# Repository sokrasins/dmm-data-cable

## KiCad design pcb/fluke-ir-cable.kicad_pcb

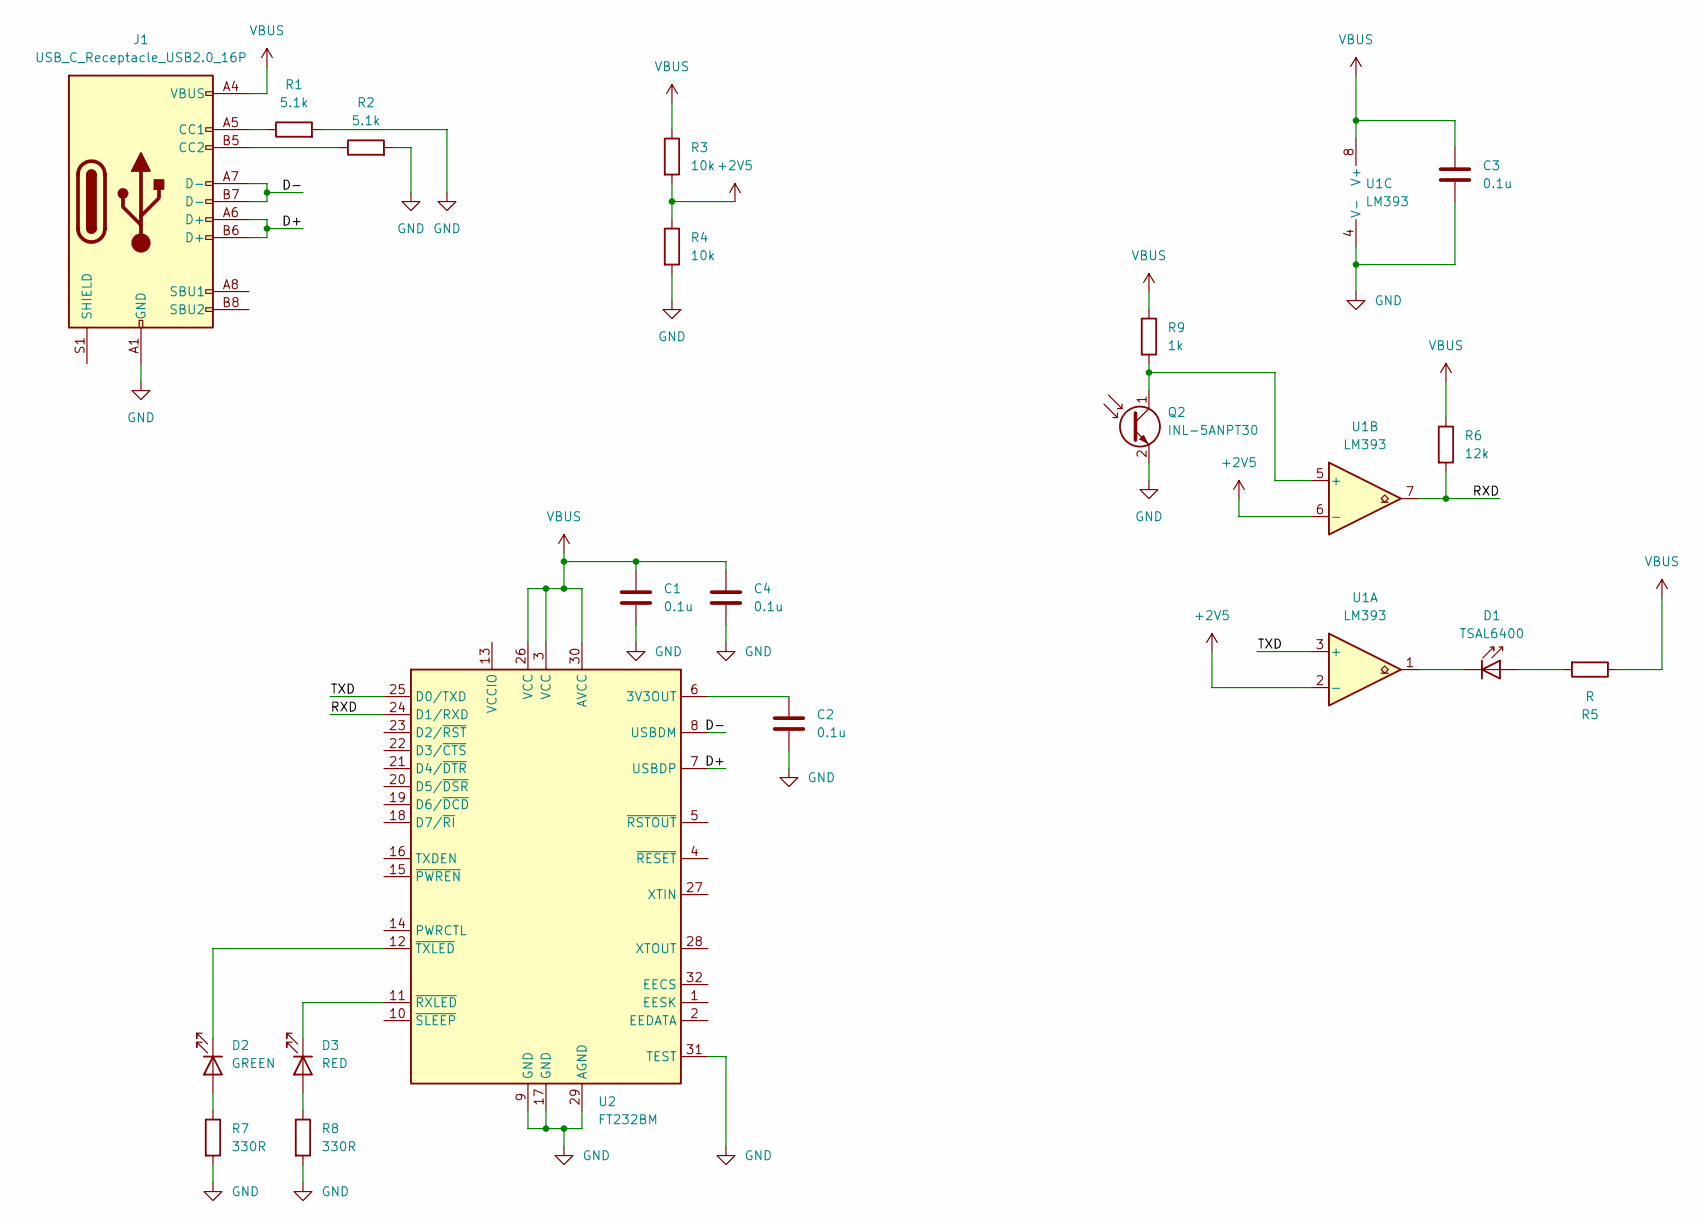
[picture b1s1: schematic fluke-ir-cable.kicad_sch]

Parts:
C1, C2, C3, C4: 0.1u; C_0603_1608Metric_Pad1.08x0.95mm_HandSolder
D1: TSAL6400; LED_D5.0mm_Clear
D2: GREEN; LED_0201_0603Metric_Pad0.64x0.40mm_HandSolder
D3: RED; LED_0201_0603Metric_Pad0.64x0.40mm_HandSolder
J1: USB_C_Receptacle_USB2.0_16P; USB_C_Receptacle_GCT_USB4105-xx-A_16P_TopMnt_Horizontal
Q2: INL-5ANPT30; LED_D5.0mm_Clear
R1, R2: 5.1k; R_0603_1608Metric_Pad0.98x0.95mm_HandSolder
R3, R4: 10k; R_0603_1608Metric_Pad0.98x0.95mm_HandSolder
R5: R; R_0603_1608Metric_Pad0.98x0.95mm_HandSolder
R6: 12k; R_0603_1608Metric_Pad0.98x0.95mm_HandSolder
R7, R8: 330R; R_0603_1608Metric_Pad0.98x0.95mm_HandSolder
R9: 1k; R_0603_1608Metric_Pad0.98x0.95mm_HandSolder
U1: LM393; TSSOP-8_4.4x3mm_P0.65mm
U2: FT232BM; LQFP-32_7x7mm_P0.8mm

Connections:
+2V5: R3.2, R4.1, U1.2 (-), U1.6 (-)
/D+: J1.A6 (D+), J1.B6 (D+), U2.7 (USBDP)
/D-: J1.A7 (D-), J1.B7 (D-), U2.8 (USBDM)
/RXD: R6.2, U1.7, U2.24 (D1/RXD)
/TXD: U1.3 (+), U2.25 (D0/TXD)
GND: C1.2, C2.2, C3.2, C4.2, J1.A1 (GND), J1.A12 (GND), J1.B1 (GND), J1.B12 (GND), Q2.2 (E), R1.2, R2.2, R4.2, R7.2, R8.2, U1.4 (V-), U2.9 (GND), U2.17 (GND), U2.29 (AGND), U2.31 (TEST)
unnamed: D1.2 (A), R5.2
unnamed: D1.1 (K), U1.1
unnamed: D2.2 (A), R7.1
unnamed: D2.1 (K), U2.12 (~TXLED)
unnamed: D3.2 (A), R8.1
unnamed: D3.1 (K), U2.11 (~RXLED)
unnamed: J1.A5 (CC1), R1.1
unnamed: J1.B5 (CC2), R2.1
unnamed: Q2.1 (C), R9.2, U1.5 (+)
unnamed: C2.1, U2.6 (3V3OUT)
VBUS: C1.1, C3.1, C4.1, J1.A4 (VBUS), J1.A9 (VBUS), J1.B4 (VBUS), J1.B9 (VBUS), R3.1, R5.1, R6.1, R9.1, U1.8 (V+), U2.3 (VCC), U2.26 (VCC), U2.30 (AVCC)

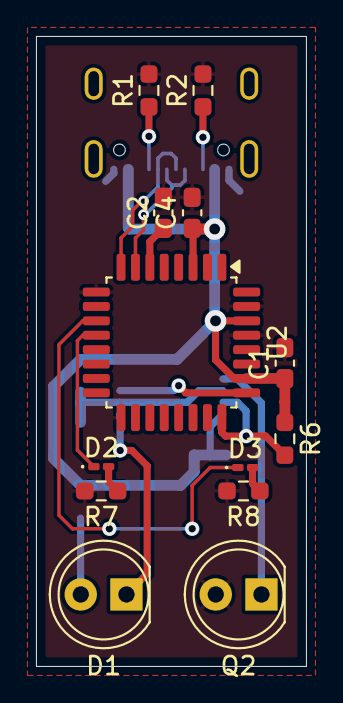
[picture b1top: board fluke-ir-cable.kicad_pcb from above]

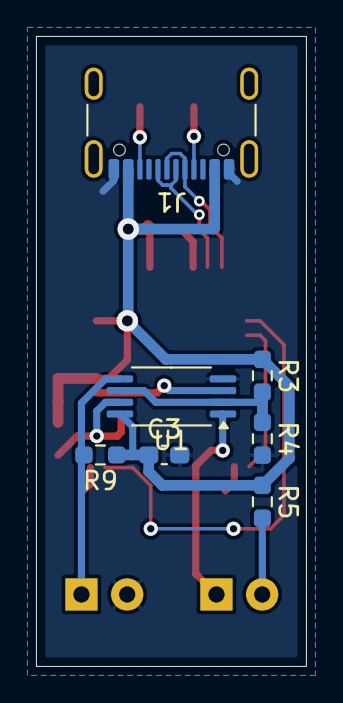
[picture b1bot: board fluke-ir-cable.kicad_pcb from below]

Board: 2 copper layers, 15.0 x 35.0 mm, 20 parts (7 on the bottom side), 17 nets.

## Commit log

2025-03-29 Layout
